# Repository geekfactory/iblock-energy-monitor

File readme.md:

# iBlock Energy Monitor

Proyecto que permite conectar un sensor de voltaje y corriente no invasivos a un Arduino a través del conector estándar iBlock. 

Este sistema se desarrolló para experimentar con la medición de corriente, voltaje, potencia en corriente alterna, tal como se muestra en el sistema __Open Energy Monitor__.

Para mayor información de este proyecto, recomendamos visitar:

* https://learn.openenergymonitor.org/

## Periféricos y características

* Conector estándar de 10 pines IDC-10 con distribución de conector iBlock
* Conector jack tipo barril (para plug invertido) permite conectar sensor de voltaje (transformador)
* Conector tipo bornera permite conectar sensor de voltaje (transformador)
* Conector jack de 3.5 mm permite conectar sensor de corriente no invasivo
* Circuitos de polarización para preparar la señal para la entrada analógica
* Se puede llevar la señal del sensor de voltaje a los pines A0 y A2
* Se puede llevar la señal del sensor de corriente a los pines A1 y A3
* Circuito impreso con tamaño estándar de 5 cm
* Se recomienda usar el sensor de corriente SCT-013-000
* Se requiere un transformador de sensado de voltaje

## Contenido del repositorio

1. __root__ - Archivos fuente de EAGLE para esta placa
2. __/documents__ - Documentación adicional, hojas de datos de componentes e instrucciones de ensamble
3. __/production__ - Histórico de gerbers enviados a producción
4. __/extras__ - Dibujos técnicos, hardware de montaje adicional y diseños de accesorios relacionados
4. __/firmware__ - Si existe el firmware de prueba o definitivo de esta placa

## Versiones del Hardware

* 1.0 - Versión inicial

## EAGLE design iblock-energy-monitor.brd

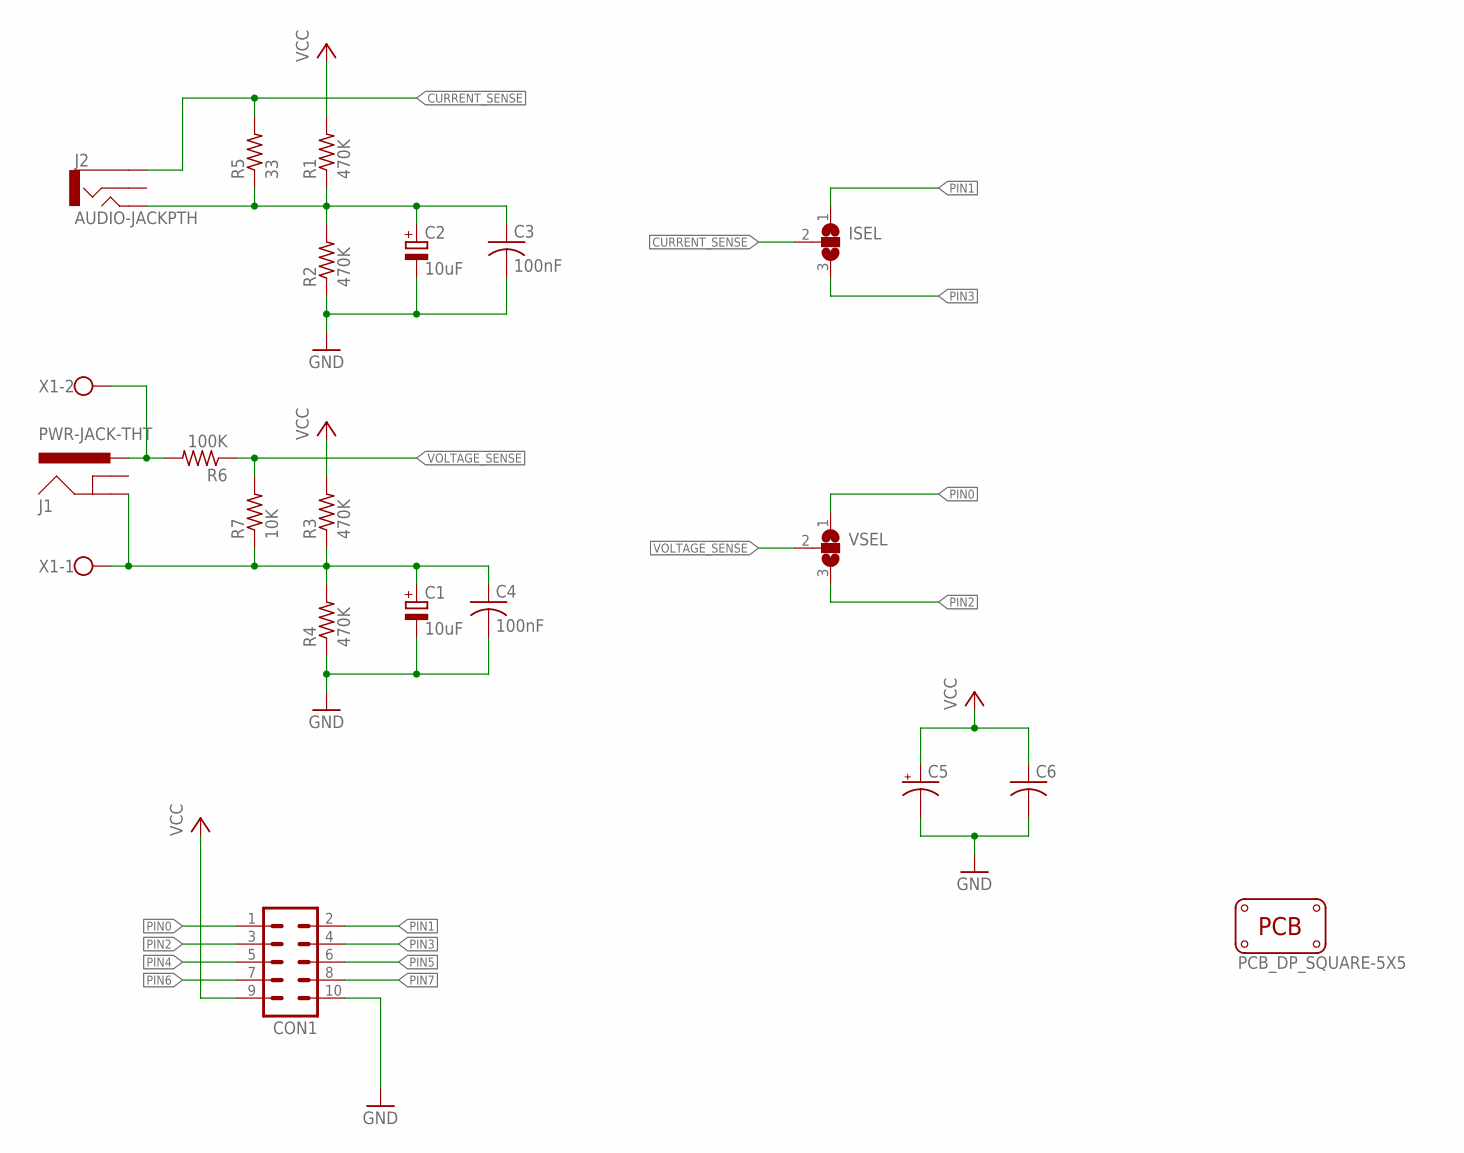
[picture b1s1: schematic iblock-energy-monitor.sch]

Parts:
C1, C2: 10uF; E2,5-5
C3, C4: 100nF; C050-024X044
C5: CPOL-USE3.5-8; E3,5-8
C6: C-US050-024X044; C050-024X044
CON1: MA05-2S; MA05-2
ISEL: SJ2W; SJ_2
J1: PWR-JACK-THT; THT-PWR-JACK
J2: AUDIO-JACKPTH; AUDIO-JACK
PCB1: PCB_DP_SQUARE-5X5; DP5050_V1
R1, R2, R3, R4: 470K; 0207/10
R5: 33; 0207/10
R6: 100K; 0207/10
R7: 10K; 0207/10
VSEL: SJ2W; SJ_2
X1: W237-102

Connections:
CURRENT_SENSE: ISEL.2, J2.1, R5.2
GND: C1.-, C2.-, C3.2, C4.2, C5.-, C6.2, CON1.10, R2.1, R4.1
unnamed: C1.+, C4.1, J1.GND, R3.1, R4.2, R7.1, X1.1
unnamed: C2.+, C3.1, J2.5, R1.1, R2.2, R5.1
unnamed: J1.PWR, R6.2, X1.2
PIN0: CON1.1, VSEL.1
PIN1: CON1.2, ISEL.1
PIN2: CON1.3, VSEL.3
PIN3: CON1.4, ISEL.3
PIN4: CON1.5
PIN5: CON1.6
PIN6: CON1.7
PIN7: CON1.8
VCC: C5.+, C6.1, CON1.9, R1.2, R3.2
VOLTAGE_SENSE: R6.1, R7.2, VSEL.2

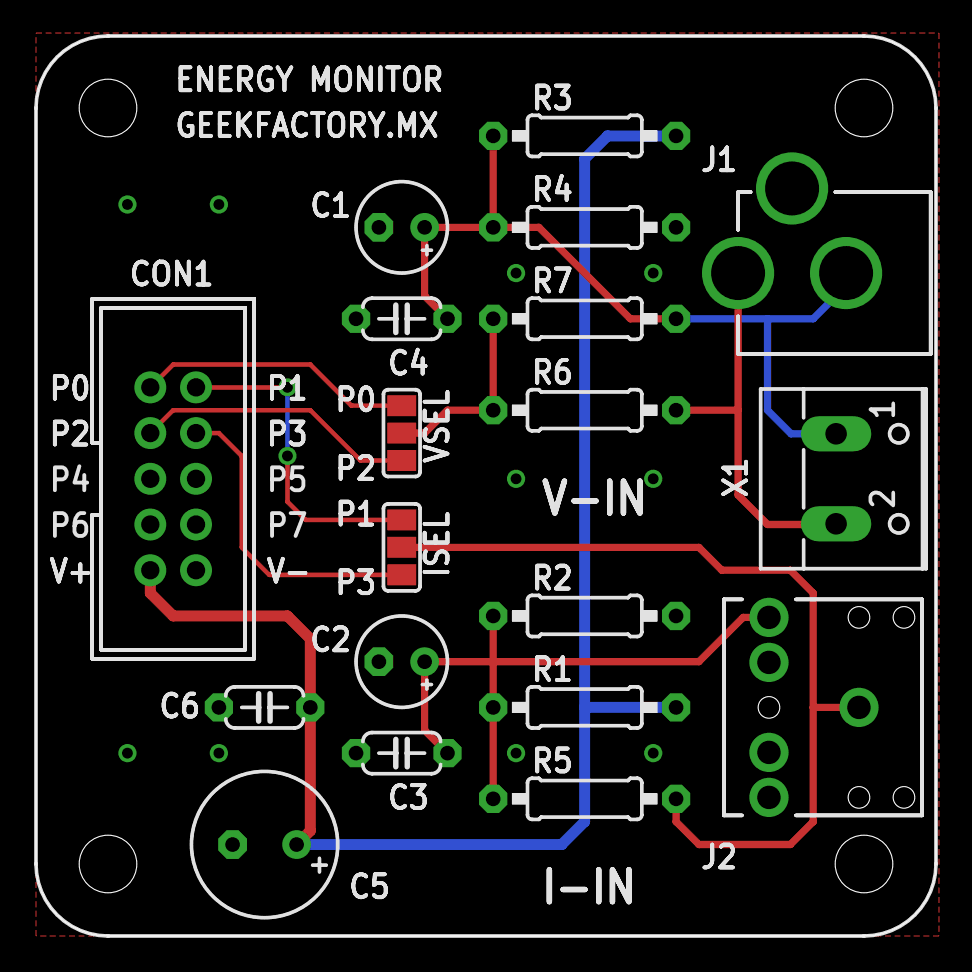
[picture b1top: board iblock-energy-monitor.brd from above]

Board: 2 copper layers, 50.0 x 50.0 mm, 20 parts (0 on the bottom side), 11 nets.

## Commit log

2020-04-12 Change license
